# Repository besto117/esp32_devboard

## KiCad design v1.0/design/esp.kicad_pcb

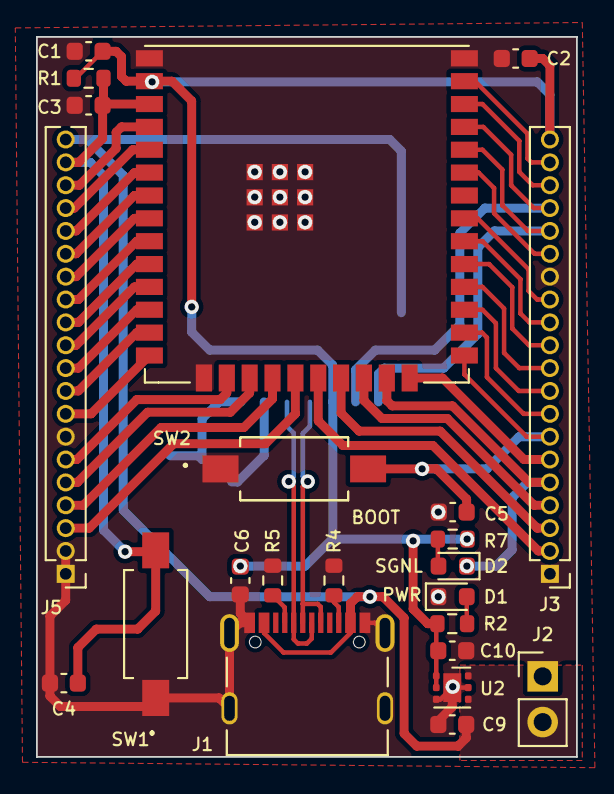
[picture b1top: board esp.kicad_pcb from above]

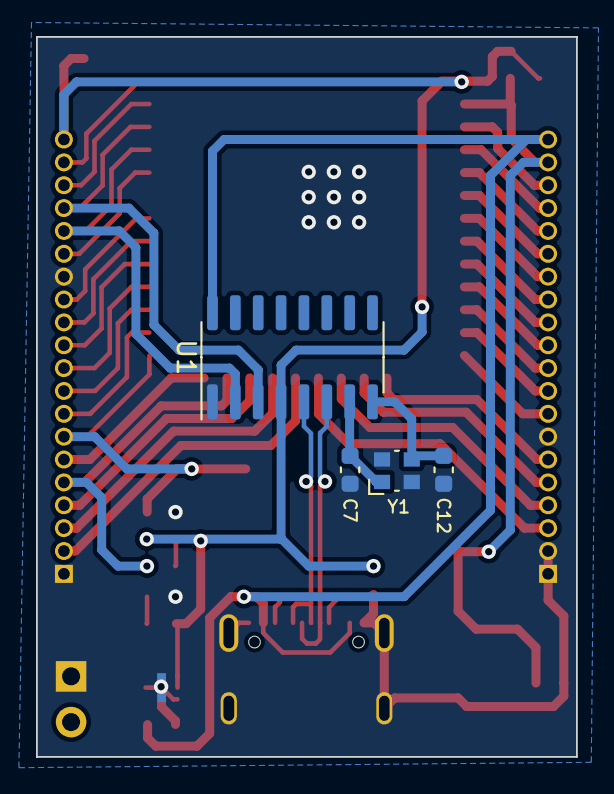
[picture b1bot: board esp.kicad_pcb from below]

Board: 2 copper layers, 30.0 x 40.0 mm, 27 parts (4 on the bottom side), 44 nets.

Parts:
C1, C3, C4, C5: .1uF; C_0603_1608Metric
C2: 22uF/16V; C_0603_1608Metric
C6: 10nF; C_0603_1608Metric
C7, C12: 22pF; C_0603_1608Metric
C9: 1uF; C_0603_1608Metric
C10: 2.2uF; C_0603_1608Metric
D1, D2: LED; LED_0603_1608Metric
J1: 12402012E212A; AMPHENOL_12402012E212A
J2: 5v INPUT; PinHeader_1x02_P2.54mm_Vertical
J3, J5: Conn_01x20; PinHeader_1x20_P1.27mm_Vertical
R1: 10K; R_0603_1608Metric
R2, R7: 330R; R_0603_1608Metric
R4, R5: 5.1K; R_0603_1608Metric
SW1, SW2: PTS636_SM43_SMTR_LFS; PTS636SM43SMTRLFS
U1: CH340G; SOIC-16_3.9x9.9mm_P1.27mm
U2: TLV76733DRVx; WSON-6-1EP_2x2mm_P0.65mm_EP1x1.6mm_ThermalVias
U4: ESP32-WROOM-32; ESP32-WROOM-32E
Y1: 12Mz; Crystal_SMD_Abracon_ABM10-4Pin_2.5x2.0mm

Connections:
+3.3V: C1.1, C2.1, C6.1, C10.2, J3.20, R1.1, R2.1, R7.1, U1.4 (V3), U2.1 (OUT), U2.2 (SNS), U4.2 (3V3)
+5V: C9.2, J1.A4_B9 (VBUS), J1.B4_A9 (VBUS), J2.2, J5.20, U1.16 (VCC), U2.4 (EN), U2.6 (IN)
/CC1: J1.A5 (CC1_A), R5.1
/CC2: J1.B5 (CC1_B), R4.1
/D+: J1.A6 (D+_A), J1.B6 (D+_B), U1.5 (UD+)
/D-: J1.A7 (D-_A), J1.B7 (D-_B), U1.6 (UD-)
CLK: J3.2, U4.20 (SCK/CLK)
CMD: J5.3, U4.19 (SCS/CMD)
EN: C3.1, C4.1, J5.19, R1.2, SW1.2 (NO), U4.3 (EN)
GND: C1.2, C2.2, C3.2, C4.2, C5.2, C6.2, C7.2, C9.1, C10.1, C12.2, D1.1 (K), J1.A1_B12 (GND), J1.B1_A12 (GND), J1.SH1 (SHIELD), J1.SH2 (SHIELD), J1.SH3 (SHIELD), J1.SH4 (SHIELD), J2.1, J3.1, J3.14, J5.1, J5.2, J5.7, R4.2, R5.2, SW1.1 (COM), SW2.1 (COM), U1.1 (GND), U2.3 (GND), U2.5 (GND), U2.7 (PAD), U4.1 (GND), U4.15 (GND), U4.38 (GND), U4.39 (GND), Y1.2, Y1.4
IO0: C5.1, J3.7, SW2.2 (NO), U4.25 (IO0)
IO1: J3.17, U1.3 (RXD), U4.35 (TXD0)
IO2: J3.6, U4.24 (IO2)
IO3: J3.16, U1.2 (TXD), U4.34 (RXD0)
IO4: J3.8, U4.26 (IO4)
IO5: J3.11, U4.29 (IO5)
IO12: J5.8, U4.14 (IO12)
IO13: J5.6, U4.16 (IO13)
IO14: J5.9, U4.13 (IO14)
IO15: D2.1 (K), J3.5, U4.23 (IO15)
IO16: J3.9, U4.27 (IO16)
IO17: J3.10, U4.28 (IO17)
IO18: J3.12, U4.30 (IO18)
IO19: J3.13, U4.31 (IO19)
IO21: J3.15, U4.33 (IO21)
IO22: J3.18, U4.36 (IO22)
IO23: J3.19, U4.37 (IO23)
IO25: J5.12, U4.10 (IO25)
IO26: J5.11, U4.11 (IO26)
IO27: J5.10, U4.12 (IO27)
IO32: J5.14, U4.8 (IO32)
IO33: J5.13, U4.9 (IO33)
IO34: J5.16, U4.6 (IO34)
IO35: J5.15, U4.7 (IO35)
IO36: J5.18, U4.4 (SENSOR_VP)
IO39: J5.17, U4.5 (SENSOR_VN)
unnamed: D1.2 (A), R2.2
unnamed: D2.2 (A), R7.2
unnamed: C7.1, U1.7 (XI), Y1.1
unnamed: C12.1, U1.8 (XO), Y1.3
SD0: J3.3, U4.21 (SDO/SD0)
SD1: J3.4, U4.22 (SDI/SD1)
SD2: J5.5, U4.17 (SHD/SD2)
SD3: J5.4, U4.18 (SWP/SD3)

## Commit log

2023-07-07 Partial schematic is done
2023-07-16 Schematic and pcb design is done
